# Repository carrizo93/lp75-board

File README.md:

# sg75
 A custom low-profile 75% mechanical keyboard, named after my time in Singapore.

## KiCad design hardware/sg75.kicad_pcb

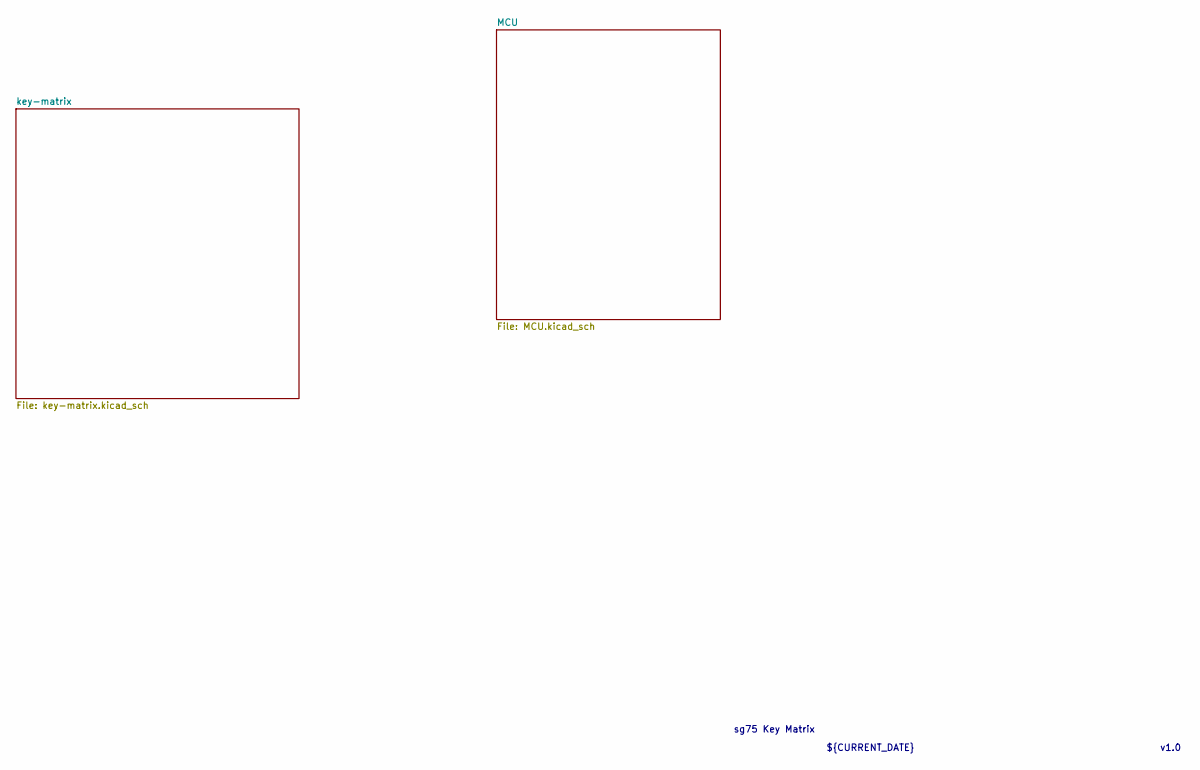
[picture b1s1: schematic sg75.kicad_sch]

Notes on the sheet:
sg75 Key Matrix
v1.0
${CURRENT_DATE}

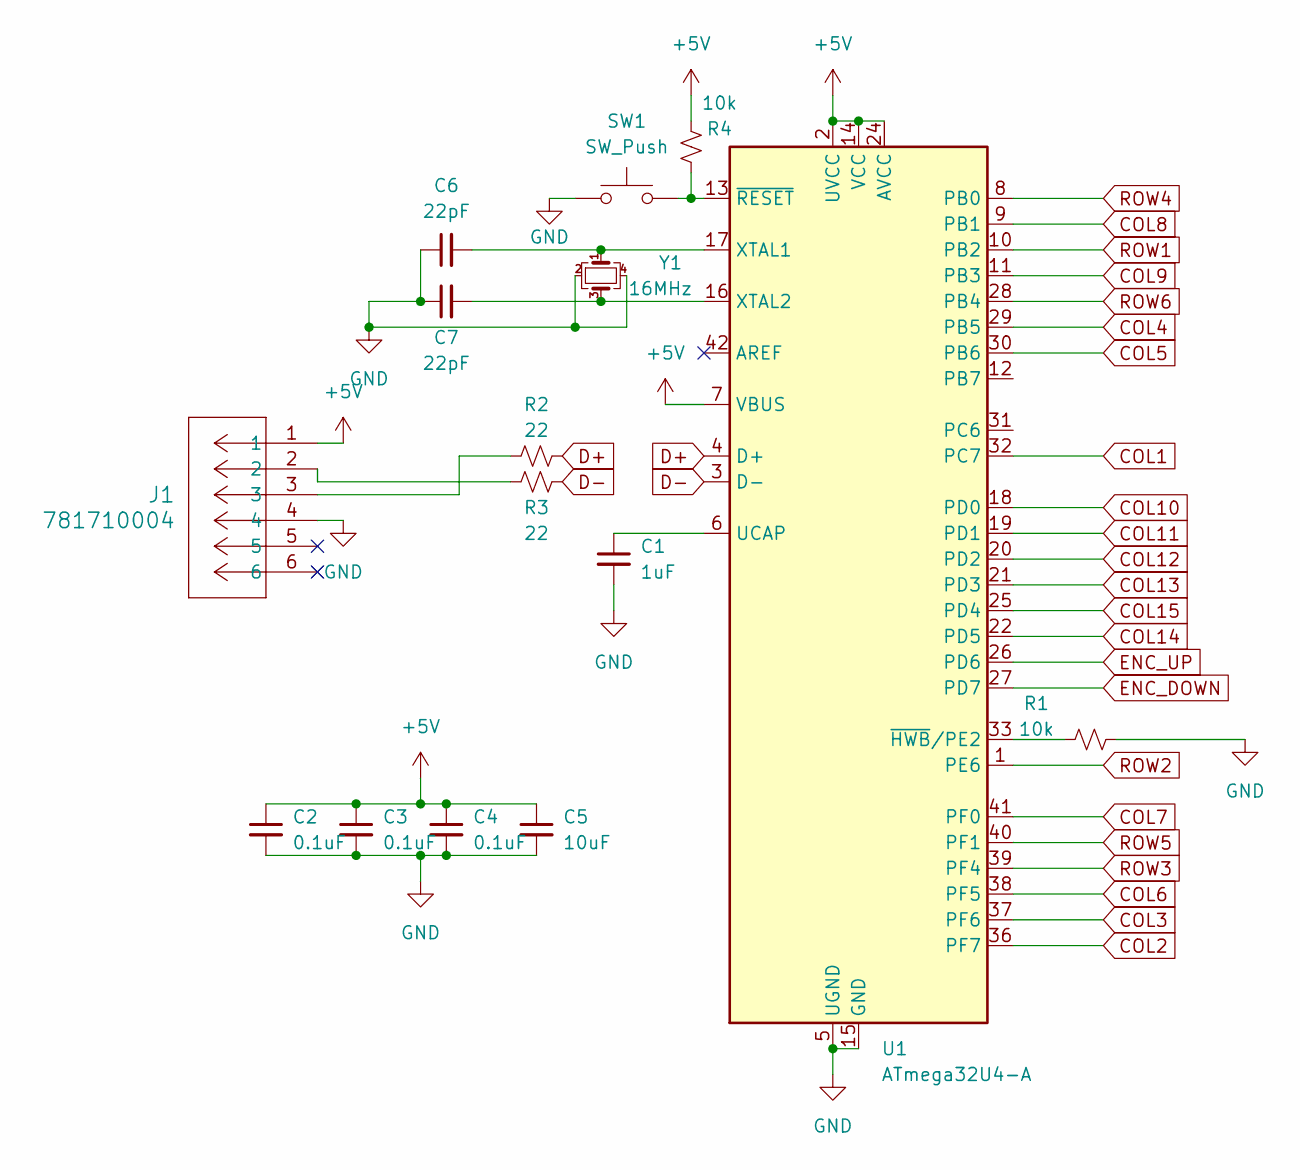
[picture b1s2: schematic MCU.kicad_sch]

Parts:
C1: 1uF; C_0805_2012Metric
C2, C3, C4: 0.1uF; C_0805_2012Metric
C5: 10uF; C_0805_2012Metric
C6, C7: 22pF; C_0805_2012Metric
J1: 781710004; CON_781710004
R1, R4: 10k; R_0805_2012Metric
R2, R3: 22; R_0805_2012Metric
SW1: SW_Push; SKQG-1155865
U1: ATmega32U4-A; TQFP-44_10x10mm_P0.8mm
Y1: 16MHz; Crystal_SMD_3225-4Pin_3.2x2.5mm

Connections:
+5V: C2.1, C3.1, C4.1, C5.1, J1.1, R4.2, U1.2 (UVCC), U1.7 (VBUS), U1.14 (VCC), U1.24 (AVCC), U1.34 (VCC), U1.44 (AVCC)
COL1: U1.32 (PC7); also elsewhere on the board
COL2: U1.36 (PF7); also elsewhere on the board
COL3: U1.37 (PF6); also elsewhere on the board
COL4: U1.29 (PB5); also elsewhere on the board
COL5: U1.30 (PB6); also elsewhere on the board
COL6: U1.38 (PF5); also elsewhere on the board
COL7: U1.41 (PF0); also elsewhere on the board
COL8: U1.9 (PB1); also elsewhere on the board
COL9: U1.11 (PB3); also elsewhere on the board
COL10: U1.18 (PD0); also elsewhere on the board
COL11: U1.19 (PD1); also elsewhere on the board
COL12: U1.20 (PD2); also elsewhere on the board
COL13: U1.21 (PD3); also elsewhere on the board
COL14: U1.22 (PD5); also elsewhere on the board
COL15: U1.25 (PD4); also elsewhere on the board
D+: R2.2, U1.4 (D+)
D-: R3.2, U1.3 (D-)
ENC_DOWN: U1.27 (PD7); also elsewhere on the board
ENC_UP: U1.26 (PD6); also elsewhere on the board
GND: C1.2, C2.2, C3.2, C4.2, C5.2, C6.1, C7.1, J1.4, R1.2, SW1.1, U1.5 (UGND), U1.15 (GND), U1.23 (GND), U1.35 (GND), U1.43 (GND), Y1.2, Y1.4; also elsewhere on the board
unnamed: J1.2, R3.1
unnamed: J1.3, R2.1
unnamed: C1.1, U1.6 (UCAP)
unnamed: C6.2, U1.17 (XTAL1), Y1.1
unnamed: C7.2, U1.16 (XTAL2), Y1.3
unnamed: R1.1, U1.33 (~HWB/PE2)
unnamed: R4.1, SW1.2, U1.13 (~RESET)
ROW1: U1.10 (PB2); also elsewhere on the board
ROW2: U1.1 (PE6); also elsewhere on the board
ROW3: U1.39 (PF4); also elsewhere on the board
ROW4: U1.8 (PB0); also elsewhere on the board
ROW5: U1.40 (PF1); also elsewhere on the board
ROW6: U1.28 (PB4); also elsewhere on the board

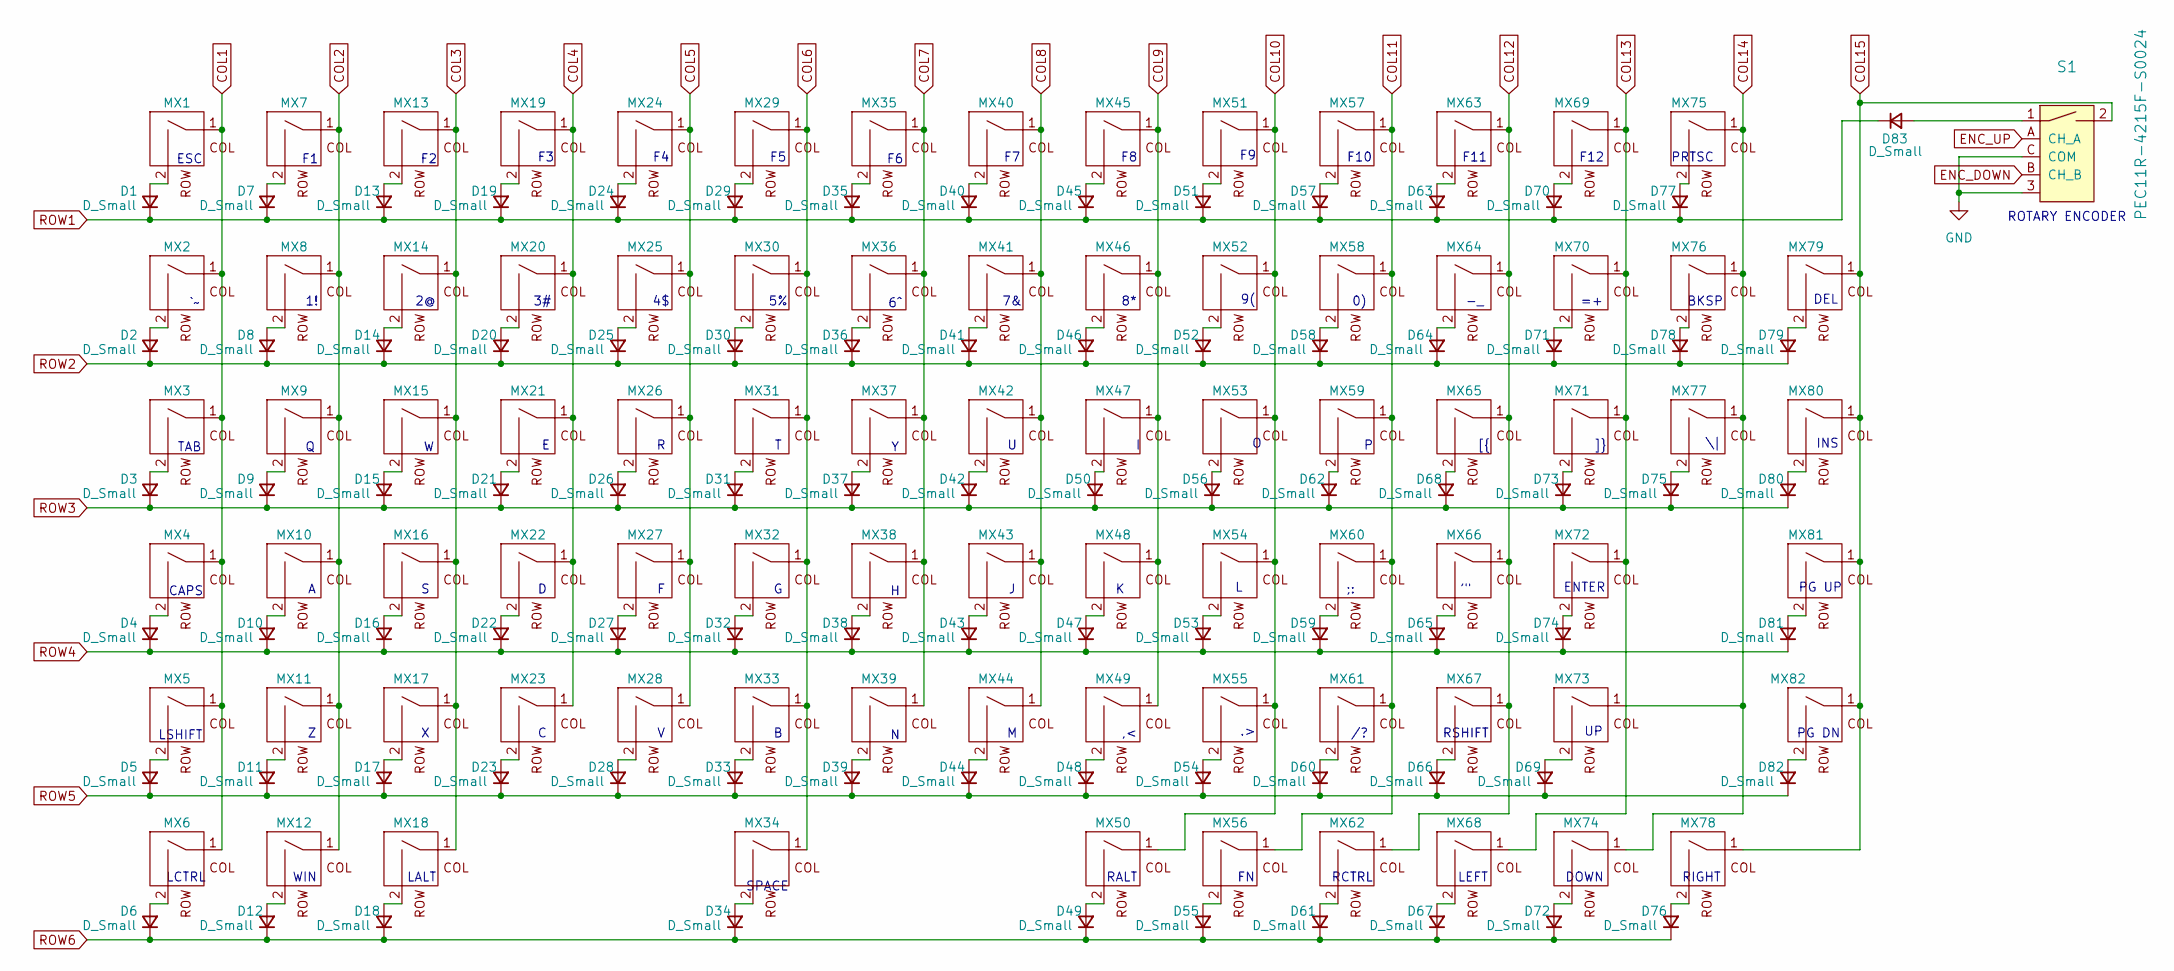
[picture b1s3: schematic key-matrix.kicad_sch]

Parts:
D1, D2, D3, D4, D5, D6, D7, D8, D9, D10, D11, D12, D13, D14, D15, D16, D17, D18, D19, D20, D21, D22, D23, D24, D25, D26, D27, D28, D29, D30, D31, D32, D33, D34, D35, D36, D37, D38, D39, D40, D41, D42, D43, D44, D45, D46, D47, D48, D49, D50, D51, D52, D53, D54, D55, D56, D57, D58, D59, D60, D61, D62, D63, D64, D65, D66, D67, D68, D69, D70, D71, D72, D73, D74, D75, D76, D77, D78, D79, D80, D81, D82, D83: D_Small; D_SOD-123
MX1, MX2, MX7, MX8, MX9, MX10, MX11, MX13, MX14, MX15, MX16, MX17, MX19, MX20, MX21, MX22, MX23, MX24, MX25, MX26, MX27, MX28, MX29, MX30, MX31, MX32, MX33, MX35, MX36, MX37, MX38, MX39, MX40, MX41, MX42, MX43, MX44, MX45, MX46, MX47, MX48, MX49, MX50, MX51, MX52, MX53, MX54, MX55, MX56, MX57, MX58, MX59, MX60, MX61, MX62, MX63, MX64, MX65, MX66, MX68, MX69, MX70, MX71, MX73, MX74, MX75, MX78, MX79, MX80, MX81, MX82: Kailh-PG1353-Solderable-1U
MX3, MX77: Kailh-PG1353-Solderable-1.5U
MX4, MX67: Kailh-PG1353-Solderable-1.75U
MX5, MX72: Kailh-PG1353-Solderable-2.25U
MX6, MX12, MX18: Kailh-PG1353-Solderable-1.25U
MX34: Kailh-PG1353-Solderable-6.25U
MX76: Kailh-PG1353-Solderable-2U
S1: PEC11R-4215F-S0024; Rotary_Encoder_Switched_PEC11R; MPN PEC11R-4215F-S0024; Digi-Key_PN PEC11R-4215F-S0024-ND

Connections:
COL1: MX1.1, MX2.1, MX3.1, MX4.1, MX5.1, MX6.1; also elsewhere on the board
COL2: MX7.1, MX8.1, MX9.1, MX10.1, MX11.1, MX12.1; also elsewhere on the board
COL3: MX13.1, MX14.1, MX15.1, MX16.1, MX17.1, MX18.1; also elsewhere on the board
COL4: MX19.1, MX20.1, MX21.1, MX22.1, MX23.1; also elsewhere on the board
COL5: MX24.1, MX25.1, MX26.1, MX27.1, MX28.1; also elsewhere on the board
COL6: MX29.1, MX30.1, MX31.1, MX32.1, MX33.1, MX34.1; also elsewhere on the board
COL7: MX35.1, MX36.1, MX37.1, MX38.1, MX39.1; also elsewhere on the board
COL8: MX40.1, MX41.1, MX42.1, MX43.1, MX44.1; also elsewhere on the board
COL9: MX45.1, MX46.1, MX47.1, MX48.1, MX49.1; also elsewhere on the board
COL10: MX50.1, MX51.1, MX52.1, MX53.1, MX54.1, MX55.1; also elsewhere on the board
COL11: MX56.1, MX57.1, MX58.1, MX59.1, MX60.1, MX61.1; also elsewhere on the board
COL12: MX62.1, MX63.1, MX64.1, MX65.1, MX66.1, MX67.1; also elsewhere on the board
COL13: MX68.1, MX69.1, MX70.1, MX71.1, MX72.1; also elsewhere on the board
COL14: MX73.1, MX74.1, MX75.1, MX76.1, MX77.1; also elsewhere on the board
COL15: MX78.1, MX79.1, MX80.1, MX81.1, MX82.1, S1.2; also elsewhere on the board
ENC_DOWN: S1.B (CH_B); also elsewhere on the board
ENC_UP: S1.A (CH_A); also elsewhere on the board
GND: S1.3, S1.C (COM); also elsewhere on the board
unnamed: D1.2 (A), MX1.2
unnamed: D2.2 (A), MX2.2
unnamed: D3.2 (A), MX3.2
unnamed: D4.2 (A), MX4.2
unnamed: D5.2 (A), MX5.2
unnamed: D6.2 (A), MX6.2
unnamed: D7.2 (A), MX7.2
unnamed: D8.2 (A), MX8.2
unnamed: D9.2 (A), MX9.2
unnamed: D10.2 (A), MX10.2
unnamed: D11.2 (A), MX11.2
unnamed: D12.2 (A), MX12.2
unnamed: D13.2 (A), MX13.2
unnamed: D14.2 (A), MX14.2
unnamed: D15.2 (A), MX15.2
unnamed: D16.2 (A), MX16.2
unnamed: D17.2 (A), MX17.2
unnamed: D18.2 (A), MX18.2
unnamed: D19.2 (A), MX19.2
unnamed: D20.2 (A), MX20.2
unnamed: D21.2 (A), MX21.2
unnamed: D22.2 (A), MX22.2
unnamed: D23.2 (A), MX23.2
unnamed: D24.2 (A), MX24.2
unnamed: D25.2 (A), MX25.2
unnamed: D26.2 (A), MX26.2
unnamed: D27.2 (A), MX27.2
unnamed: D28.2 (A), MX28.2
unnamed: D29.2 (A), MX29.2
unnamed: D30.2 (A), MX30.2
unnamed: D31.2 (A), MX31.2
unnamed: D32.2 (A), MX32.2
unnamed: D33.2 (A), MX33.2
unnamed: D34.2 (A), MX34.2
unnamed: D35.2 (A), MX35.2
unnamed: D36.2 (A), MX36.2
unnamed: D37.2 (A), MX37.2
unnamed: D38.2 (A), MX38.2
unnamed: D39.2 (A), MX39.2
unnamed: D40.2 (A), MX40.2
unnamed: D41.2 (A), MX41.2
unnamed: D42.2 (A), MX42.2
unnamed: D43.2 (A), MX43.2
unnamed: D44.2 (A), MX44.2
unnamed: D45.2 (A), MX45.2
unnamed: D46.2 (A), MX46.2
unnamed: D47.2 (A), MX48.2
unnamed: D48.2 (A), MX49.2
unnamed: D49.2 (A), MX50.2
unnamed: D50.2 (A), MX47.2
unnamed: D51.2 (A), MX51.2
unnamed: D52.2 (A), MX52.2
unnamed: D53.2 (A), MX54.2
unnamed: D54.2 (A), MX55.2
unnamed: D55.2 (A), MX56.2
unnamed: D56.2 (A), MX53.2
unnamed: D57.2 (A), MX57.2
unnamed: D58.2 (A), MX58.2
unnamed: D59.2 (A), MX60.2
unnamed: D60.2 (A), MX61.2
unnamed: D61.2 (A), MX62.2
unnamed: D62.2 (A), MX59.2
unnamed: D63.2 (A), MX63.2
unnamed: D64.2 (A), MX64.2
unnamed: D65.2 (A), MX66.2
unnamed: D66.2 (A), MX67.2
unnamed: D67.2 (A), MX68.2
unnamed: D68.2 (A), MX65.2
unnamed: D69.2 (A), MX73.2
unnamed: D70.2 (A), MX69.2
unnamed: D71.2 (A), MX70.2
unnamed: D72.2 (A), MX74.2
unnamed: D73.2 (A), MX71.2
unnamed: D74.2 (A), MX72.2
unnamed: D75.2 (A), MX77.2
unnamed: D76.2 (A), MX78.2
unnamed: D77.2 (A), MX75.2
unnamed: D78.2 (A), MX76.2
unnamed: D79.2 (A), MX79.2
unnamed: D80.2 (A), MX80.2
unnamed: D81.2 (A), MX81.2
unnamed: D82.2 (A), MX82.2
unnamed: D83.2 (A), S1.1
ROW1: D1.1 (K), D7.1 (K), D13.1 (K), D19.1 (K), D24.1 (K), D29.1 (K), D35.1 (K), D40.1 (K), D45.1 (K), D51.1 (K), D57.1 (K), D63.1 (K), D70.1 (K), D77.1 (K), D83.1 (K); also elsewhere on the board
ROW2: D2.1 (K), D8.1 (K), D14.1 (K), D20.1 (K), D25.1 (K), D30.1 (K), D36.1 (K), D41.1 (K), D46.1 (K), D52.1 (K), D58.1 (K), D64.1 (K), D71.1 (K), D78.1 (K), D79.1 (K); also elsewhere on the board
ROW3: D3.1 (K), D9.1 (K), D15.1 (K), D21.1 (K), D26.1 (K), D31.1 (K), D37.1 (K), D42.1 (K), D50.1 (K), D56.1 (K), D62.1 (K), D68.1 (K), D73.1 (K), D75.1 (K), D80.1 (K); also elsewhere on the board
ROW4: D4.1 (K), D10.1 (K), D16.1 (K), D22.1 (K), D27.1 (K), D32.1 (K), D38.1 (K), D43.1 (K), D47.1 (K), D53.1 (K), D59.1 (K), D65.1 (K), D74.1 (K), D81.1 (K); also elsewhere on the board
ROW5: D5.1 (K), D11.1 (K), D17.1 (K), D23.1 (K), D28.1 (K), D33.1 (K), D39.1 (K), D44.1 (K), D48.1 (K), D54.1 (K), D60.1 (K), D66.1 (K), D69.1 (K), D82.1 (K); also elsewhere on the board
ROW6: D6.1 (K), D12.1 (K), D18.1 (K), D34.1 (K), D49.1 (K), D55.1 (K), D61.1 (K), D67.1 (K), D72.1 (K), D76.1 (K); also elsewhere on the board

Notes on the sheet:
RCTRL
F12
F11
PG DN
RALT
SPACE
RSHIFT
ROTARY ENCODER
LSHIFT
CAPS
WIN
ESC
PRTSC
BKSP
RIGHT
LCTRL
LALT
INS
F10
TAB
PG UP
LEFT
DOWN
DEL
ENTER

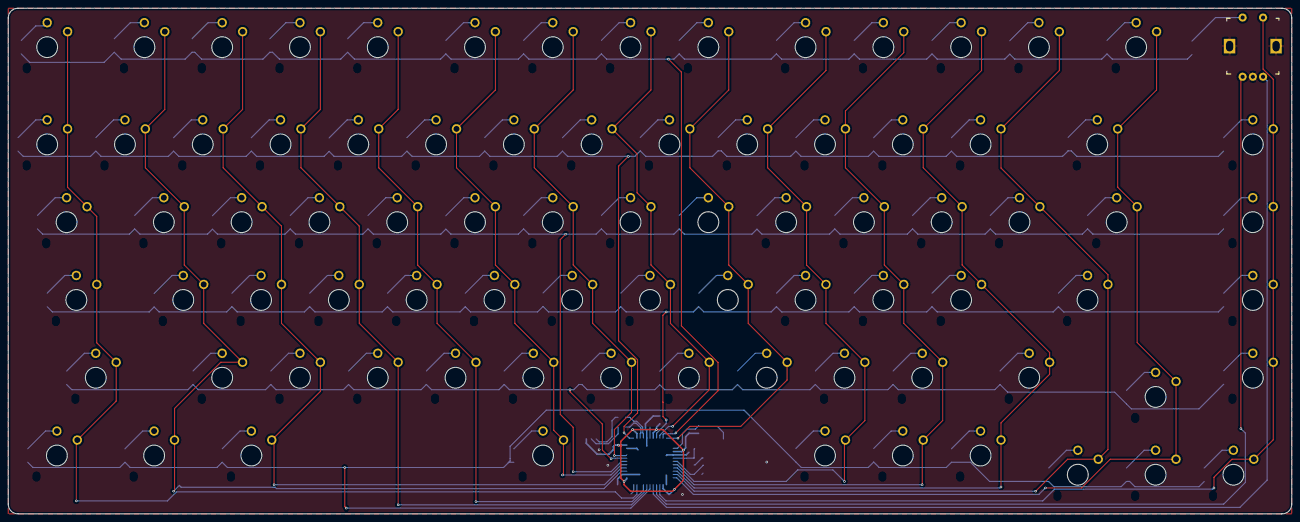
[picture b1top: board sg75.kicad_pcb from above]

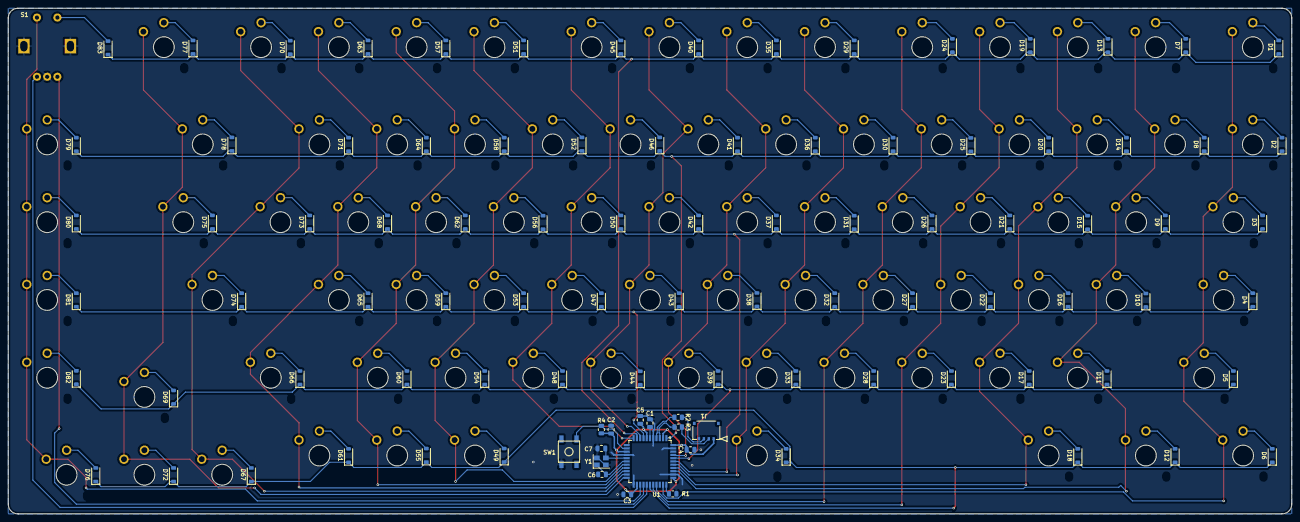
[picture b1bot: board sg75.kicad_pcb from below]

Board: 2 copper layers, 314.3 x 123.8 mm, 181 parts (98 on the bottom side), 117 nets.

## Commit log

2024-10-08 add submodules
2024-10-08 start project
2024-10-13 plan out and wire key layout
2024-11-18 begin pcb design
2024-11-18 update submodules
2024-11-18 update libraries add kle json
2024-11-24 finish pcb
